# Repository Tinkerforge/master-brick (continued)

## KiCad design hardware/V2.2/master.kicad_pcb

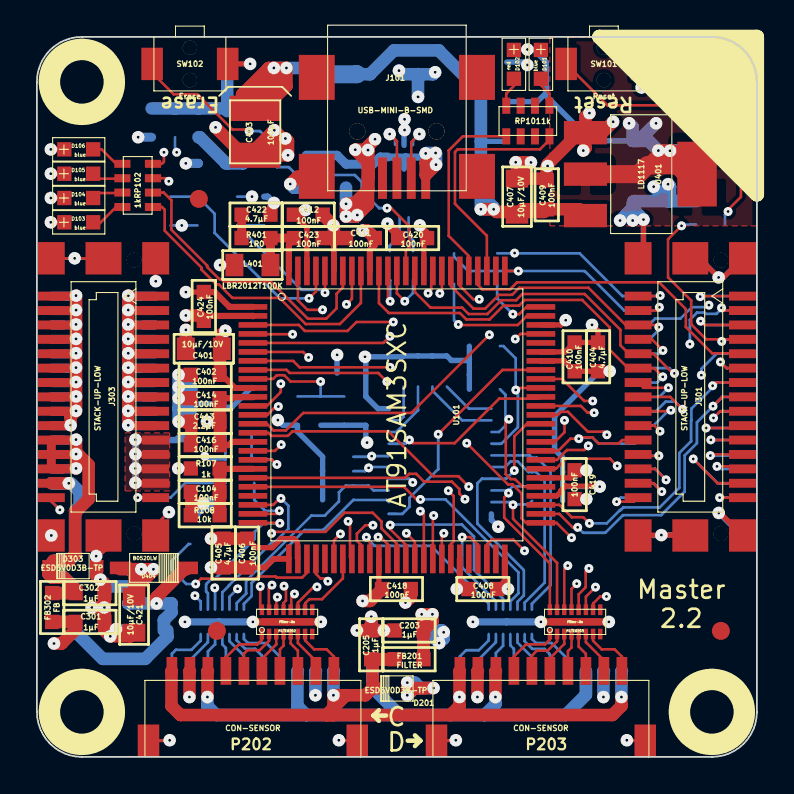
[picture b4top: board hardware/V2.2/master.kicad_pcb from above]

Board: 4 copper layers, 40.0 x 40.0 mm, 124 parts (0 on the bottom side), 146 nets.

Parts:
C101, C103, C201, C203, C204, C205, C206, C301, C302, C303, C304: 1µF; 0603
C102, C104, C202, C402, C406, C408, C409, C410, C411, C412, C414, C416, C417, C418, C419, C420, C423, C424: 100nF; 0603
C105, C106: DNP; 0603
C401, C407, C415, C421, C425: 10µF/10V; 0805
C403: 100µF; 3528-21
C404, C405, C422: 4.7µF; 0603
C413: 2.2µF; 0603
D101, D103, D104, D105, D106: blue; D0603
D102: red; D0603
D201, D303: ESD5V0D3B-TP; SOD-323
D202: ESD3V3D3B-TP; SOD-323
D301, D302, D304: TVS 3V3; SOD-323
D401: PMEG4050; SOD-128
D402: Z5V; MiniMelf
D403: Z3.3V; MiniMelf
D404: B0520LW; SOD-123
F101: PTC; 1206
FB101, FB102, FB302, FB303: FB; 0603
FB201, FB202: FILTER; 0603
FB301: 0; 0805
FILTER201, FILTER202, FILTER203, FILTER204: Filter-8x; DFN16-33x135
Fiducial_Mark: VAL**; Fiducial_Mark
Fiducial_Mark#2, Fiducial_Mark#3, Fiducial_Mark#4, Fiducial_Mark#5, Fiducial_Mark#6: VAL**; Fiducial_Mark
J101: USB-MINI-B-SMD
J102, J103, J104, J105: DRILL; DRILL_NP
J301, J303: STACK-UP-LOW; BTB08-ACS-TOP
J302, J304: STACK-DOWN; BTB08-ACS-BTM
L101: 744230900; WE-CNSW-0603
L401: LBR2012T100K; 0805
P201, P202, P203, P204: CON-SENSOR
P401: TSTPT_GND; TSTPT
P402: TSTPT_5V; TSTPT
P403: TSTPT_3V3; TSTPT
R101, R102: 27; 0603
R103, R108, R402: 10k; 0603
R104, R107, R301: 1k; 0603
R105: 27k; 0603
R106: 18k; 0603
R302, R303: 10; 0603
R304: 100k; 0603
R401: 1R0; 0603
RP101, RP102, RP301: 1k; 0603X4
RP201: 10k; 0603X4
RP202, RP203, RP204: 2k2; 0603X4
SW101: Reset; TACT-SWITCH
SW102: Erase; TACT-SWITCH
U101: AT91SAM3SXC; LQFP100
U102: 82400152; SOT563-SPEC
U201: PCA9518PW; TSSOP20
U401: LD1117; SOT-223
U402: RT9701XB; SOT23-5
VAL: WEEE_7mm_back
VAL#2: CE_5mm
X101: 16Mhz; CRYSTAL_3225

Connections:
3V3: C201.2, C202.2, C204.2, C401.1, C402.1, C404.1, C405.1, C406.1, C408.1, C410.1, C411.1, C412.1, C415.1, C417.1, C421.1, C424.1, D101.1, D102.1, D103.1, D104.1, D105.1, D106.1, D403.2, D404.1, FB202.1, P403.1, R103.2, R107.2, RP201.1, RP201.2, RP201.3, RP201.4, RP202.1, RP202.2, RP202.3, RP202.4, RP203.1, RP203.2, RP203.3, RP203.4, RP204.1, RP204.2, RP204.3, RP204.4, SW102.2, U101.1, U101.10, U101.27, U101.50, U101.54, U101.69, U101.91, U101.98, U201.20, U401.2, U402.3
3V3-EN: R402.1, U101.28, U402.4
BRICKLET-I2C-SCL: RP202.8, U101.55, U201.3
BRICKLET-I2C-SDA: RP202.5, U101.66, U201.4
BRICKLET-IO0_0/AD0: FILTER204.13, U101.23
BRICKLET-IO0_1: FILTER204.12, U101.38
BRICKLET-IO0_2/PWM0: FILTER204.11, U101.25
BRICKLET-IO0_3: FILTER204.10, U101.37
BRICKLET-IO1_0/AD1: FILTER201.13, U101.21
BRICKLET-IO1_1: FILTER201.12, U101.39
BRICKLET-IO1_2/PWM1: FILTER201.11, U101.47
BRICKLET-IO1_3: FILTER201.10, U101.35
BRICKLET-IO2_0/AD2: FILTER202.13, U101.4
BRICKLET-IO2_1/DA0: FILTER202.12, U101.93
BRICKLET-IO2_2/PWM2: FILTER202.11, U101.43
BRICKLET-IO2_3: FILTER202.10, U101.32
BRICKLET-IO3_0/AD3: FILTER203.13, U101.6
BRICKLET-IO3_1/DA1: FILTER203.12, U101.99
BRICKLET-IO3_2/PWM3: FILTER203.11, U101.40
BRICKLET-IO3_3: FILTER203.10, U101.29
BRICKLET-SEL-0: FILTER204.14, U101.58, U201.14
BRICKLET-SEL-1: FILTER201.14, U101.62, U201.7
BRICKLET-SEL-2: FILTER202.14, U101.65, U201.17
BRICKLET-SEL-3: FILTER203.14, U101.68, U201.11
GND: C101.2, C102.2, C103.2, C104.2, C105.2, C106.2, C201.1, C202.1, C203.1, C204.1, C205.1, C206.1, C301.2, C302.2, C303.2, C304.2, C401.2, C402.2, C403.2, C404.2, C405.2, C406.2, C407.2, C408.2, C409.2, C410.2, C411.2, C412.2, C413.2, C414.2, C415.2, C416.2, C417.2, C418.2, C419.2, C420.2, C421.2, C422.2, C423.2, C424.2, C425.2, D201.1, D202.1, D301.1, D302.1, D303.1, D304.1, D402.1, D403.1, FB101.1, FB301.2, FILTER201.EXP, FILTER202.EXP, FILTER203.EXP, FILTER204.EXP, J101.5, J301.EP, J302.EP, J303.EP, J304.EP, P201.2, P201.EP, P202.2, P202.EP, P203.2, P203.EP, P204.2, P204.EP, P401.1, R104.1, R105.1, R108.1, R304.1, R402.2, SW101.2, U101.2, U101.26, U101.45, U101.70, U101.73, U101.95, U102.2, U201.10, U401.1, U402.2, X101.3
LED1: RP102.1, U101.92
LED2: RP102.2, U101.94
LED3: RP102.3, U101.13
LED4: RP102.4, U101.17
unnamed: C101.1, F101.2, FB102.1
unnamed: C102.1, R103.1, R104.2, U101.9
unnamed: C104.1, R107.1, R108.2, U101.19
unnamed: C205.2, D201.2, FB201.2, P201.1, P202.1, P203.1, P204.1
unnamed: C206.2, D202.2, FB202.2, P201.3, P202.3, P203.3, P204.3
unnamed: C302.1, D303.2, FB302.2, J303.22, J303.24, J303.26, J304.22, J304.24, J304.26
unnamed: C303.1, D304.2, FB303.1, J303.28, J304.28
unnamed: C413.1, C414.1, C416.1, C418.1, C419.1, C420.1, L401.1, U101.11, U101.16, U101.36, U101.56, U101.85
unnamed: C422.1, R401.1
unnamed: C423.1, L401.2, R401.2, U101.100
unnamed: D101.2, RP101.1
unnamed: D102.2, RP101.4
unnamed: D103.2, RP102.8
unnamed: D104.2, RP102.7
unnamed: D105.2, RP102.6
unnamed: D106.2, RP102.5
unnamed: F101.1, J101.1, U102.5
unnamed: FB101.2, J101.6
unnamed: FB301.1, J303.21, J303.23, J303.25, J303.27, J304.21, J304.23, J304.25, J304.27
unnamed: FILTER201.1, P201.4
unnamed: FILTER201.2, P201.5
unnamed: FILTER201.3, P201.6
unnamed: FILTER201.4, P201.7
unnamed: FILTER201.5, P201.8
unnamed: FILTER201.6, P201.9
unnamed: FILTER201.7, P201.10
unnamed: FILTER201.15, RP204.7, U201.6
unnamed: FILTER201.16, RP204.8, U201.5
unnamed: FILTER202.1, P202.4
unnamed: FILTER202.2, P202.5
unnamed: FILTER202.3, P202.6
unnamed: FILTER202.4, P202.7
unnamed: FILTER202.5, P202.8
unnamed: FILTER202.6, P202.9
unnamed: FILTER202.7, P202.10
unnamed: FILTER202.15, RP203.5, U201.16
unnamed: FILTER202.16, RP203.6, U201.15
unnamed: FILTER203.1, P203.4
unnamed: FILTER203.2, P203.5
unnamed: FILTER203.3, P203.6
unnamed: FILTER203.4, P203.7
unnamed: FILTER203.5, P203.8
unnamed: FILTER203.6, P203.9
unnamed: FILTER203.7, P203.10
unnamed: FILTER203.15, RP204.5, U201.9
unnamed: FILTER203.16, RP204.6, U201.8
unnamed: FILTER204.1, P204.4
unnamed: FILTER204.2, P204.5
unnamed: FILTER204.3, P204.6
unnamed: FILTER204.4, P204.7
unnamed: FILTER204.5, P204.8
unnamed: FILTER204.6, P204.9
unnamed: FILTER204.7, P204.10
unnamed: FILTER204.15, RP203.7, U201.13
unnamed: FILTER204.16, RP203.8, U201.12
unnamed: J101.2, U102.3
unnamed: J101.3, U102.1
unnamed: J301.7, J302.7, R301.1
unnamed: J303.1, J303.3, J303.5, J303.7, J303.9, J303.11, J303.13, J303.15, J303.17, J303.19, J304.1, J304.3, J304.5, J304.7, J304.9, J304.11, J304.13, J304.15, J304.17, J304.19
unnamed: J303.2, J303.4, J303.6, J303.8, J303.10, J303.12, J303.14, J303.16, J303.18, J303.20, J304.2, J304.4, J304.6, J304.8, J304.10, J304.12, J304.14, J304.16, J304.18, J304.20
unnamed: J303.29, J304.29, R302.1
unnamed: J303.30, J304.30, R303.1, R304.2
unnamed: L101.1, U102.6
unnamed: L101.2, R102.1
unnamed: L101.3, R101.1
unnamed: L101.4, U102.4
unnamed: R101.2, U101.88
unnamed: R102.2, U101.89
unnamed: RP101.5, U101.80
unnamed: RP101.8, U101.78
unnamed: RP201.5, U201.1
unnamed: RP201.6, U201.2
unnamed: RP201.7, U201.18
unnamed: RP201.8, U201.19
unnamed: SW102.1, U101.87
SCL-PULLUP: RP301.4, U101.74
SDA-PULLUP: RP301.1, U101.75
STACK-CURRENT: D301.2, R302.2, U101.24
STACK-EX-0-GP00: J301.19, J302.19, U101.48
STACK-EX-0-GP01: J301.21, J302.21, U101.44
STACK-EX-0-GP02: J301.23, J302.23, U101.57
STACK-EX-1-GP00: J301.25, J302.25, U101.72
STACK-EX-1-GP01: J301.27, J302.27, U101.64
STACK-EX-1-GP02: J301.29, J302.29, U101.81
STACK-HIGH/JTAG-TMS: J301.9, U101.79
STACK-I2C-SCL/JTAG-TDO: J301.4, J302.4, RP301.5, U101.76
STACK-I2C-SDA/JTAG-TDI: J301.2, J302.2, RP301.8, U101.51
STACK-MASTER-DETECT: J302.9, U101.14
STACK-RESET: R301.2, SW101.1, U101.60
STACK-SELECT-00: J301.6, J302.8, U101.82
STACK-SELECT-01: J301.8, J302.10, U101.84
STACK-SELECT-02: J301.10, J302.12, U101.86
STACK-SELECT-03: J301.12, J302.14, U101.90
STACK-SELECT-04: J301.14, J302.16, U101.3
STACK-SELECT-05: J301.16, J302.18, U101.5
STACK-SELECT-06: J301.18, J302.20, U101.7
STACK-SELECT-07: J301.20, U101.8
STACK-SELECT-EX-00: J301.22, J302.22, U101.59
STACK-SELECT-EX-01: J301.24, J302.24, U101.63
STACK-SER2-RTS: J301.30, J302.30, U101.34
STACK-SER2-RXD: J301.26, J302.26, U101.15
STACK-SER2-TXD: J301.28, J302.28, U101.20
STACK-SER-RXD: J301.13, J302.13, U101.53
STACK-SER-SCK: J301.17, J302.17, U101.67
STACK-SER-TXD: J301.15, J302.15, U101.52
STACK-SPI-MISO: J301.1, J302.1, U101.41
STACK-SPI-MOSI: J301.3, J302.3, U101.33
STACK-SPI-SCLK: J301.5, J302.5, U101.31
STACK-SPI-SELECT: J302.6, U101.42
STACK-SYNC/JTAG-TCK: J301.11, J302.11, U101.83
STACK-VOLTAGE: D302.2, R303.2, U101.18
USB-DETECT: R106.2, U101.12
VPP: C304.1, C425.1, D404.2, FB303.2, U402.1, U402.5
VSTACK: C203.2, C301.1, C403.1, C407.1, C409.1, D401.2, D402.2, FB201.1, FB302.1, P402.1, U401.3
VUSB: C103.1, D401.1, FB102.2, R105.2, R106.1
XIN: C106.1, U101.97, X101.2
XOUT: C105.1, U101.96, X101.1

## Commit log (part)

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2011-08-25 initial hardware source commit
2011-08-25 add project description
2011-08-26 add voltage threshold for current and voltage getter
2011-08-26 change diode PMEG1020EH -> B0520LW-7-F
2011-09-08 4 times blinkenlights to give stack participants more time for bricklet discovery
2011-09-08 new calculation for voltage epsilon (again..)
2011-09-14 limit line length of java examples to 100 characters
2011-09-26 change pulldown to default, pulldown is done in hardware here
2011-09-26 fix current multiplier (was wrong by factor 2)
2011-10-05 add tinkerforge package to python imports
2011-10-06 add firmware version and name
2011-11-14 Add first Master code for Chibi, works for one to one communication, api might change again!
2012-02-13 checkin of version 1.1 of master brick: - add missing pulldown resistor - add fiducial markers
2012-02-14 first working version of chibi protocol
2012-02-21 add frequency and channel setter and getter
2012-03-11 Add USB request detection to allow Chibi Slave stack to be powered over USB
2012-03-11 Fix bug with ADC calibration readout (through bricklib)
2012-03-20 update version
2012-03-28 fix serveral chibi bugs
2012-04-17 remove rs485_init.c
2012-05-09 Add PHP examples
2012-05-25 Add Ruby example
2012-06-12 Prefer IPConnection destroy over join_thread
2012-06-27 Add RS485 resync mode, better RS485 enumerate retries
2012-07-01 Add generate_makefile.bat for windows
2012-07-02 Add usb hotplug support (through bricklib)
2012-07-24 Use dynamically caluclated timeouts for RS485
2012-07-24 Add WIFI include
2012-07-25 Fix unit of stack current in C/C++ example
2012-08-01 Send empty message if slave has timeout, to allow slave to process buffer
2012-08-28 Add WIFI configuration functionality (WIP!)
2012-09-07 Ignore temporary build files
2012-09-12 Update to led_blink change in bricklib
2012-09-12 First code for WPA Enterprise support (write/read of certificate missing)
2012-09-14 Disable debug output
2012-09-15 Generalize mac and ip parsing, fix bug in gw parsing
2012-09-17 turn AT+WRXPS on and off with sleep mode, better handling for AT+NSTCP, add support for async messages and turn them on by default
2012-09-18 Add V1.3 to changelog (WIFI Extension support)
2012-09-19 Add receive ringbuffer (prevent oveflow due to callbacks)
2012-09-24 Add support for Ad Hoc and Access Point mode
2012-09-26 Set regulatory domain also in current configuration
2012-10-04 Extend .gitignore
2012-10-04 Use WSEC=1 instead of auth mode = open for no encryption (seems to work better)
2012-10-04 Add new version and changelog
2012-10-06 Fix bug in RS485 code (rs485 recv pin was set by wifi code) remove unused adc averaging code
2012-10-10 Remove unused define
2012-10-16 Fix mixup between Ad Hoc DHCP and AP Static IP
2012-10-16 Fix Chibi Extension initialization sequence
2012-10-24 Make cmake find the correct objcopy binary
    On some systems cmake uses the wrong objcopy binary, tell it to use
    the correct one.
2012-10-26 Fix bugs in Ethernet recv/send, add DHCP client implementation, add general brickd for wifi and Ethernet
    Still missing (Ethernet): API, user configuration, EEPROM write/read of configuration
2012-11-13 const correctness and other small improvements
2012-11-13 Add protocol 2.0 capability for brickd on master and WIFI Extension
2012-11-15 Add Protocol 2.0 support for RS485 Extension
2012-11-20 Fix WIFI EEPROM positions
2012-11-21 More precise voltage calculation
2012-11-22 Insert connected uid for RS485 and Chibi connections
2012-11-28 add hardware files for version 2.0
2012-11-29 Remove unused code (replaced by Protocol 2.0 routing)
2012-11-29 Make C examples Protocol 2.0 compatible
2012-11-29 Add more invalid parameter checks
2012-11-29 Make PHP examples Protocol 2.0 compatible
2012-11-30 delphi: Remove unnecessary parentheses and call destructor again
2013-01-29 Fix buffer overflow in WIFI Extension code
2013-02-06 Use different ATS configuration, parse startup/reset message, refactor data state machine
2013-02-07 Use smaller USB timeout on startup enumeration, to allow faster enumeration Dont reread the config after the first WIFI association fails
2013-02-07 Add changelog and version for 2.0.3
2013-02-12 Reset WIFI Module after disassociate from AP - Fix problem with changing of slave addresses of Chibi and RS485 Extension - Externalize WIFI ringbuffer and feed bytes in state machine byte by byte (wi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
2013-02-18 2.0.5: Reissue Low-Power-Mode after disassociate and add API for: - SetWifiHostname - GetWifiHostname - SetCurrentCallbackPeriod - GetCurrentCallbackPeriod - SetVoltageCallbackPeriod - GetVoltageCall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
2013-03-27 Make sure to always read the header completey (ethernet extension)
2013-04-04 Add forced ACK after 10ms without answer and handle WIFI xon/xoff commands of GS1011MEES
2013-04-12 Finalize Ethernet extension support
2013-06-06 increase ethernet reset holding time from 2us to 10us to ensure proper bootup for all ethernet extensions
2013-06-10 Call ethernet reset function 2 times to make sure it works allways
2013-08-13 Add shell example
2014-01-10 Add Perl examples
2014-02-07 Add Mathematica examples
2014-02-10 perl: fixed namespace
2014-02-11 javascript: short examples
2014-02-20 javascript: add html example
2014-02-24 javascript: port 4280, startExample()
2014-02-28 javascript: Break long lines and cleanup whitespace
2014-03-06 labview: Add example in LV2010 format
2014-03-18 Disable debug by default
2014-03-21 Fix bugs in DHCP implementation (thanks Martin)
2014-03-25 matlab: adding examples
2014-04-02 java: Unify constants style
2014-04-02 perl: Unify print style
2014-04-04 Fix key comparing for Ethernet authentication
2014-04-17 matlab: Change scale values to double
2014-06-12 change voltage divider values
2014-07-07 Add changelog entry
2014-07-15 java: Replace System.console() usage with an Eclipse compatible pattern
2014-08-27 Add new DMA routing
2014-10-09 add handling for master 2.1 prototype * changed master extension gp0 pin (fix flashing problem) * master 2.1 detection pin
2014-11-25 Add changelog for v2.3.0
2015-01-08 hardware version 2.1 checkin
2015-01-21 Add missing w5x00 files to make list
2015-02-13 vbnet: Use ReadLine instead of ReadKey
    Because ReadKey doesn't work with a pipe as stdin on the RED Brick.
2015-03-02 windows: Stop cmake from searching for mingw32-make.exe
    Using MinGW Makefiles as generator makes cmake search for mingw32-make.exe
    which might not be installed because GnuWin32's make.exe is used instead.
2015-03-30 route vcc signal with more border clearance
2015-04-09 c: Whitespace
2015-05-07 fix tvs diode orientation also for single tvs diode use
2015-05-19 Add changelog, increase version to 2.3.2
2015-05-26 Update to version 2.3.3
    * Reinitialize SPI state machine after initial stack enumerate
2015-06-08 description text sorted
2015-07-25 Make JavaScript browser example textarea readonly
2015-07-28 Simplify variable names in examples again
2015-08-07 Use full device class name in Python examples
2015-08-12 Fix minor warnings in C/C++ example
2015-08-18 Cleanup VB.NET examples
2015-09-07 Fix bugs in brickd implementation.
2015-09-09 Move toolchain to bricklib
2015-09-24 Generator based example cleanup
2015-11-12 matlab: Fix callback handling for R2014a
    http://undocumentedmatlab.com/blog/matlab-callbacks-for-java-events-in-r2014a
2016-03-02 Fix error in adc calibration
2016-04-08 Define _GNU_SOURCE to make string.h include strcasestr
2016-05-18 c: Add missing device destroy call
2016-06-10 Add status led api
2016-06-24 wifi-v2: Initialize WIFI Extension when entering bootloader
    But only if no WIFI Extension has been initialized yet. This help
    with the initial flashing of WIFI Extensions.
2016-06-27 Rename read/write_wifi2_flash to read/write_wifi2_serial_port
    The old name was misleading, as it gave the impression of directly
    reading and writing the flash of the ESP8266 module.
2016-06-30 Add 2.4.0 version entry to changelog
2016-07-01 Make the change UID comment more explicit
2016-08-29 Fix changelog date
2016-10-21 Fix typo in comment
2016-11-04 Add ringbuffer and co mcu c files
2016-11-24 Integrate mesh status
2017-01-06 Add COM_MESSAGE_USER_LAST_FID define (needed for newest bricklib)
2017-01-09 There is a small race condition during the socket initialization, a new socket might already be established before we can read back the SOCK_LISTEN status. So we accept the SOCK_ESTABLISHED status to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
2017-01-09 Remove date from unreleased changelog item
2017-01-18 Send not-supported error for not-supported brickd functions
2017-01-23 Add 2.4.2 changelog
2017-02-24 Use 50ms timeout instead of 250ms to reach faster reaction time in case of full buffer in WIFI Extension V2
2017-02-24 Fix bug in double buffer handling of rx peak
2017-02-24 Increase version
2017-02-24 add timeout count API changelog entry
2017-03-27 First test with StepUp script for generating .step files out of kiCAD
2017-04-19 Add PCB for netlist/3d conversion
2017-04-20 Fixed symbols D12, D13, P6, P5 and Q1
2017-04-20 Add 3d information for all parts
2017-04-20 Fix D2 from blue to red
2017-04-21 fix clearances
2017-04-21 Add new version of PCB with 3d data
2017-04-28 Fix reordered component paths
2017-05-05 Add changelog entry for wifi password getter removal
2017-05-11 Update changelog for release
2017-05-12 new master brick prototype, partially finished
2017-06-02 octave: Use javaObject instead of deprecated java_new
2017-06-02 Fix typos in comments
2017-06-28 Don't enable SPI stack debugging by default
2017-06-28 Add 2.4.5 changelog entry
2017-07-06 new master brick emi test prototype
2017-11-14 Fix indentation
2017-12-05 Add new enumeration support for Chibi
2017-12-05 Add new enumeration support for WIFI
2017-12-05 Increase version and add changelog
2017-12-08 Remove LED changes that are debug-leftovers
2017-12-08 Make CRC16 calculation more efficent.
    New implementation uses 512 byte flash more, but is about 50% faster.
2017-12-08 Remove unused eeprom slave implementation from Makefile
2017-12-13 Improve changelog for 2.4.6
2018-01-11 Add ref to changelog
2018-02-19 javascript: Close div tag correctly
2018-02-20 Cleanup KiCad libraries config
    Ensure LibDir=kicad-libraries and LibName1=tinkerforge.
    Remove special library.
2018-04-27 Add git ref to changelog
2018-07-09 Add first prototype of Makefile with docker support
    We are trying to establish better reproducable builds by using
    a fixed build environment in docker. This is currently still
    work in progress.
2018-07-11 Instead of having the Makefile in every Brick project we include it from the bricklib
2018-07-11 Remove obsolete generate_makefile scripts
2018-07-31 Increase version and update changelog
2018-09-03 Unify spelling in changelog
2018-11-07 rust: Accept host names for ip connection, fix naming inconsistencies
2018-12-18 go: Change import path.
2018-12-20 rust: Reformat examples.
2019-01-24 mqtt: Fix example header.
2019-01-24 mqtt: Remove executable bit in example permissions.
2019-01-24 mqtt: Minor example fixes.
2019-02-27 Add rev to changelog
2019-04-09 fix 3d model
2020-01-13 examples: Use python3 input instead of python2 raw_input.
2020-01-24 Fix format string warning
2020-02-12 Master v3 prototype
2020-03-10 Add support for Master Brick hardware verison 3.0
2020-03-11 Added logo "CE" and "WEEE", added testpionts for bricklet 3,3V and 5V, added second CC resistor.
2020-03-20 added filter
2020-04-01 Remove unused variable
2020-04-09 add series resistors for stack connections, change signal connections
2020-04-14 add ferrites for usb gnd and shield
2020-04-14 ordered prototype
2020-05-05 Add support for newest version of HW 3.0 prototype
    The new version changes around some Extension and Bricklet pins.
    There are no functional changes.
2020-06-22 Remove ADC calibration for Master Brick 3.0
    Master Brick 3.0 does not support the legacy 10p Bricklets,
    so there is no ADC calibration necessary anymore.
2020-09-09 specify capacitor values
2021-02-23 Add ref for 2.5.0 and proper release date
2021-03-15 fix via positions
2021-03-24 add logos, add fiducials
2021-11-05 version 3.2
    add nrst improvement
2021-11-17 add missing data
2022-01-10 add missing files
2022-01-10 fix library links in schematics
2022-01-11 * Show Master Brick 3.1 as 3.1 (3.0 was never released to public)
    * Fix mixup with extension pins
    * Make chip temperature compatible with both sam3s and sam4s (through bricklib)
2022-05-17 drc check
2022-07-19 update 3d files to master 3.0 update 3d files to master 3.0# Bitte geben Sie eine Commit-Beschreibung für Ihre Änderungen ein. Zeilen,
